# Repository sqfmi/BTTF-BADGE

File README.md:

# BTTF BADGE

Order PCBs from OSHPARK (Choose After Dark PCBs for Best Results): https://oshpark.com/projects/hdZOu9qd

## Bill of Materials
| Component               | Quantity | Link                                             |
|-------------------------|----------|--------------------------------------------------|
| LED 0603                | 24       |                                                  |
| S8050 SOT-23            | 8        |                                                  |
| 10K Resistor Array 4x0603 | 2        |https://www.digikey.com/product-detail/en/panasonic-electronic-components/EXB-38V103JV/Y9103CT-ND/256604 |
| 74HC4017 SOIC-16        | 1        |https://www.digikey.com/product-detail/en/texas-instruments/CD74HC4017M96/296-12808-1-ND/475934 |
| 74LVC1G14 SOT-353       | 1        |https://www.digikey.com/product-detail/en/diodes-incorporated/74LVC1G14SE-7/74LVC1G14SE-7CT-ND/3829423 |
| 30K Trimmer Pot         | 1        |https://www.digikey.com/product-detail/en/bourns-inc/TC33X-2-303E/TC33X-2-303ECT-ND/3437933 |
| 10uF 0805               | 1        |                                                  |
| CR2032 Battery Holder   | 1        | https://www.digikey.com/product-detail/en/keystone-electronics/3034/36-3034-ND/4499289 |
| SAO Connector           | 1        |                                                  |

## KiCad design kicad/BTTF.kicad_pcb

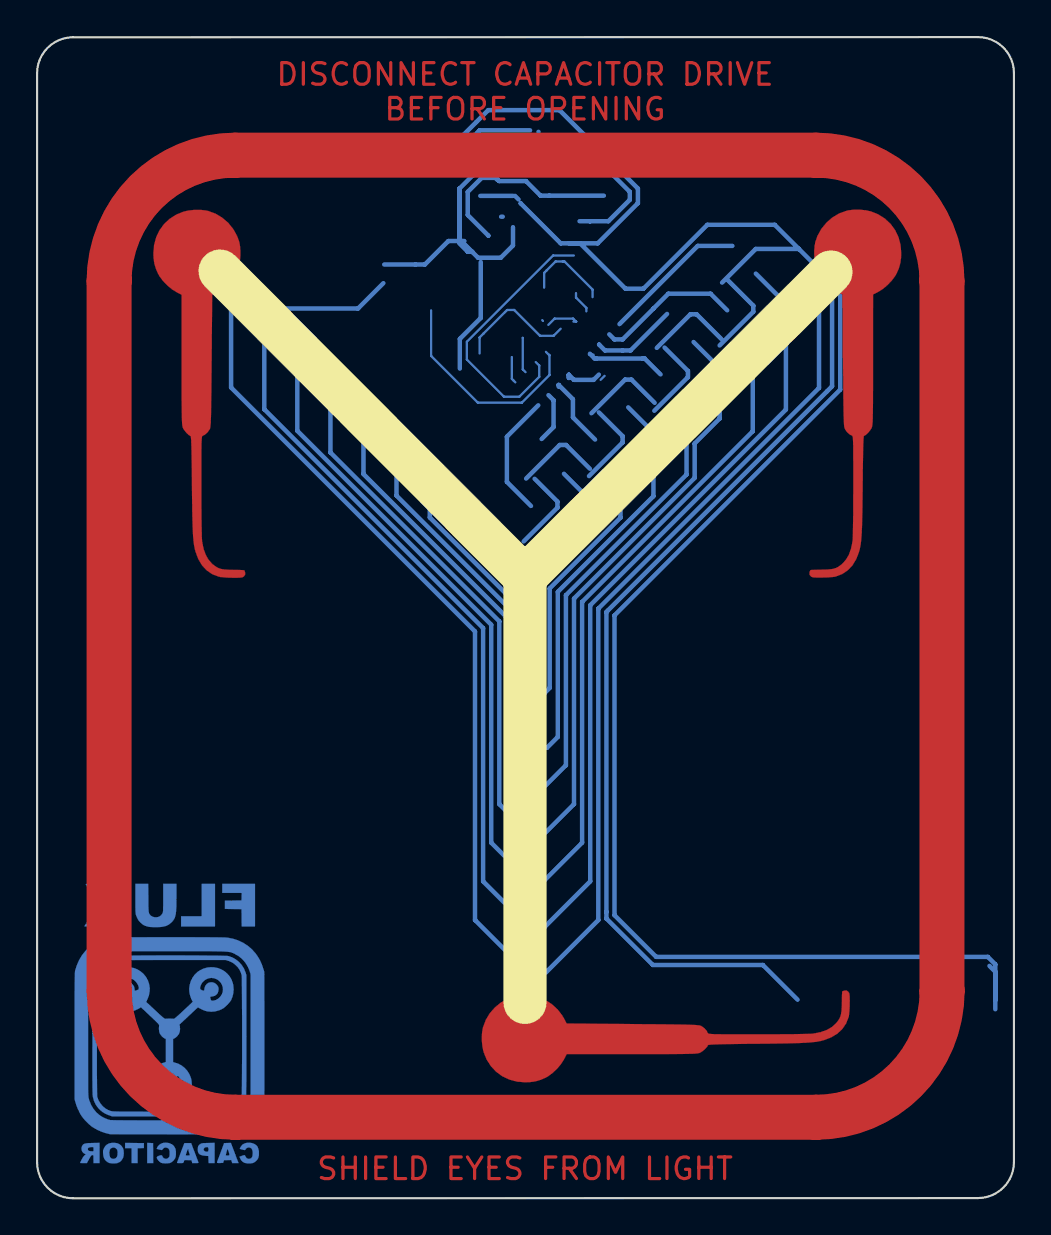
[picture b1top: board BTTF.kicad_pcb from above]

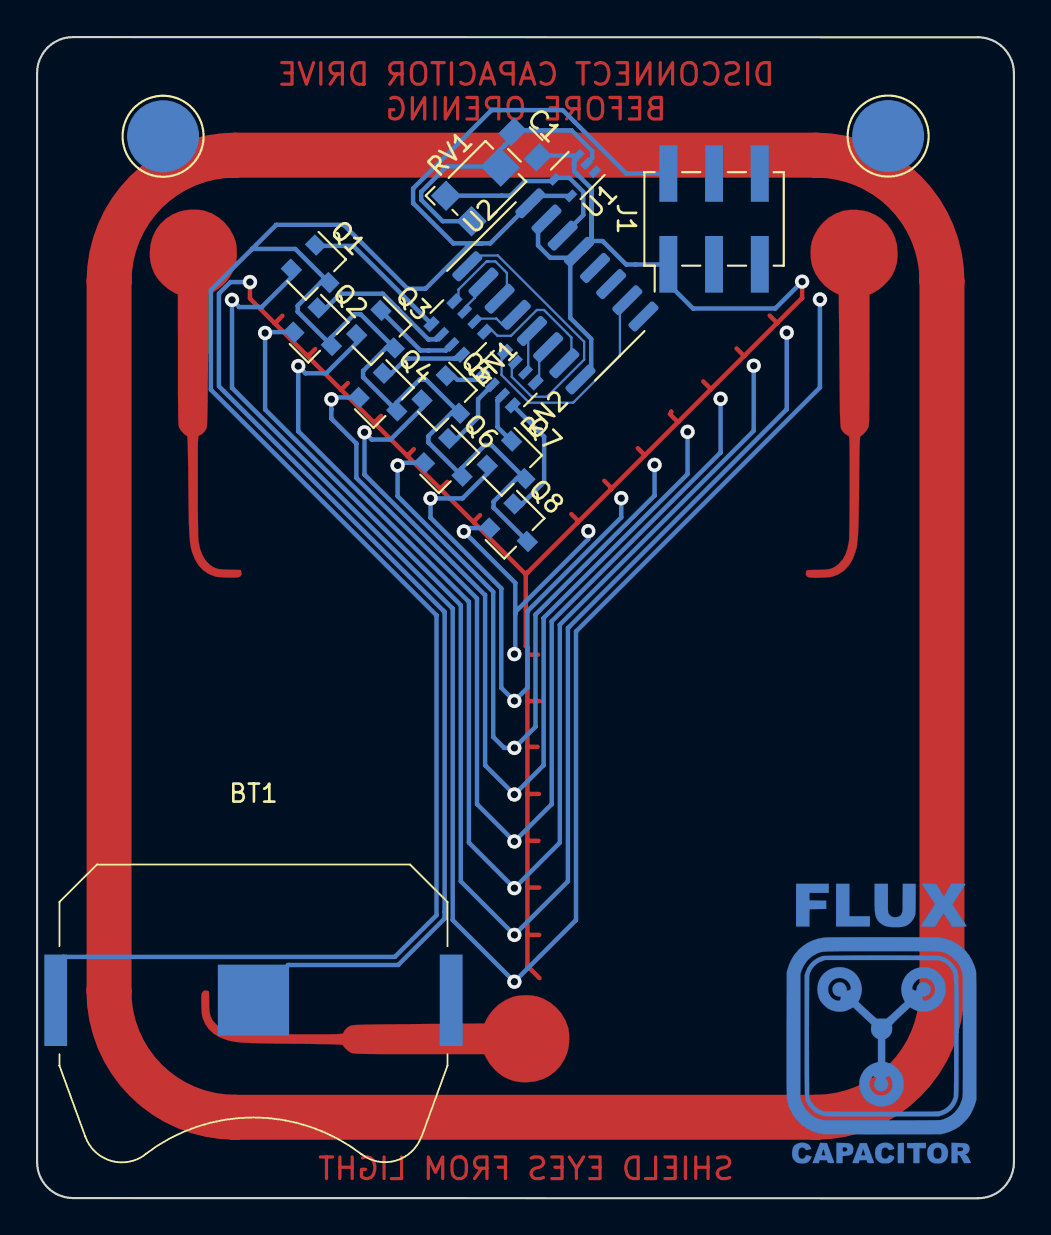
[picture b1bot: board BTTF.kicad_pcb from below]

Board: 2 copper layers, 54.3 x 64.5 mm, 40 parts (16 on the bottom side), 28 nets.

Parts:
BT1: CR2032; Keystone_3034_1x20mm-CoinCell
C1: 10uF; C_0805
D1A1, D1B1, D1C1, D2A1, D2B1, D2C1, D3A1, D3B1, D3C1, D4A1, D4B1, D4C1, D5A1, D5B1, D5C1, D6A1, D6B1, D6C1, D7A1, D7B1, D7C1, D8A1, D8B1, D8C1: LED; R_0603
J1: SAO; Pin_Header_Straight_2x03_Pitch2.54mm_SMD
Q1, Q2, Q3, Q4, Q5, Q6, Q7, Q8: S8050; SOT-23
RN1, RN2: 10K; R_Array_Convex_4x0603
RV1: 30K; Potentiometer_Bourns_TC33X_Vertical
U1: 74LVC1G14; SOT-353_SC-70-5
U2: 74HC4017; SOIC-16_3.9x9.9mm_P1.27mm

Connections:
GND: BT1.2, C1.2, D1A1.1, D1B1.1, D1C1.1, D2A1.1, D2B1.1, D2C1.1, D3A1.1, D3B1.1, D3C1.1, D4A1.1, D4B1.1, D4C1.1, D5A1.1, D5B1.1, D5C1.1, D6A1.1, D6B1.1, D6C1.1, D7A1.1, D7B1.1, D7C1.1, D8A1.1, D8B1.1, D8C1.1, J1.1, U1.3, U2.8, U2.13, U2.15
LED1: Q1.1, RN1.5
LED2: Q2.1, RN1.6
LED3: Q3.1, RN1.7
LED4: Q4.1, RN1.8
LED5: Q5.1, RN2.5
LED6: Q6.1, RN2.6
LED7: Q7.1, RN2.7
LED8: Q8.1, RN2.8
unnamed: C1.1, RV1.2, RV1.3, U1.2
unnamed: D1A1.2, D1B1.2, D1C1.2, Q1.2
unnamed: D2A1.2, D2B1.2, D2C1.2, Q2.2
unnamed: D3A1.2, D3B1.2, D3C1.2, Q3.2
unnamed: D4A1.2, D4B1.2, D4C1.2, Q4.2
unnamed: D5A1.2, D5B1.2, D5C1.2, Q5.2
unnamed: D6A1.2, D6B1.2, D6C1.2, Q6.2
unnamed: D7A1.2, D7B1.2, D7C1.2, Q7.2
unnamed: D8A1.2, D8B1.2, D8C1.2, Q8.2
unnamed: RN1.1, U2.7
unnamed: RN1.2, U2.4
unnamed: RN1.3, U2.2
unnamed: RN1.4, U2.3
unnamed: RN2.1, U2.6
unnamed: RN2.2, U2.5
unnamed: RN2.3, U2.1
unnamed: RN2.4, U2.10
unnamed: RV1.1, U1.4, U2.14
VCC: BT1.1, J1.2, Q1.3, Q2.3, Q3.3, Q4.3, Q5.3, Q6.3, Q7.3, Q8.3, U1.5, U2.16

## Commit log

2020-05-10 added files
2020-05-10 added KiCad folder
2020-05-10 removed files
2020-05-10 Create BTTF
